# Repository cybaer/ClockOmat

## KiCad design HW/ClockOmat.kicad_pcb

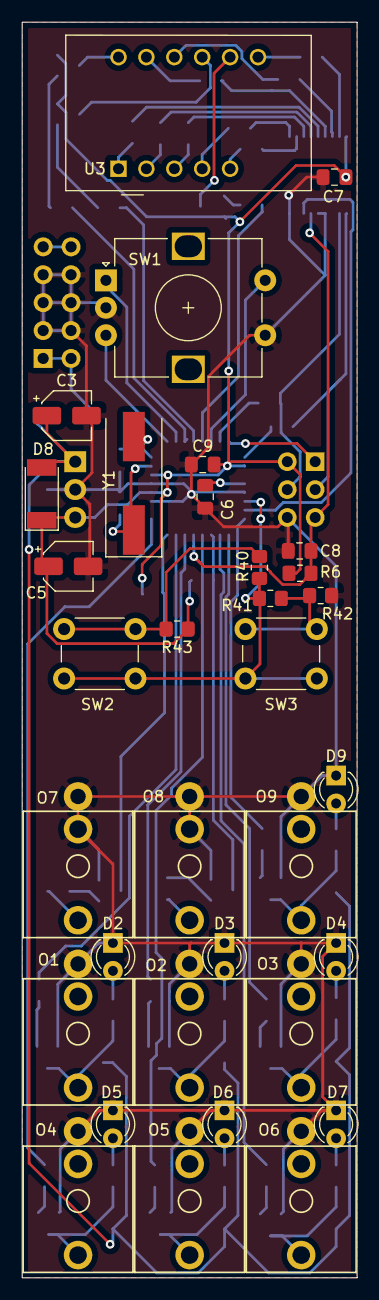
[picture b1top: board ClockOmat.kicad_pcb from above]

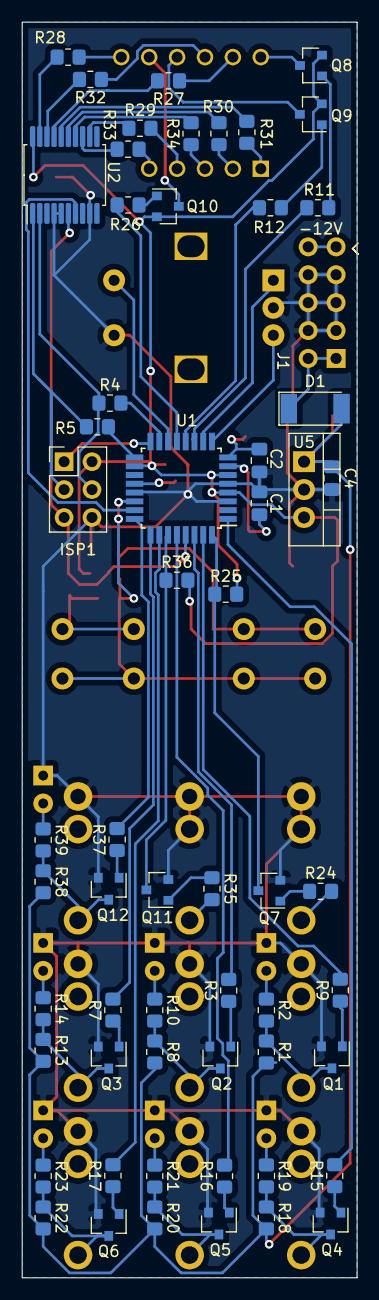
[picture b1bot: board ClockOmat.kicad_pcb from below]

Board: 2 copper layers, 30.5 x 114.3 mm, 92 parts (59 on the bottom side), 79 nets.

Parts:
C1, C2: 22p; C_0805_2012Metric_Pad1.18x1.45mm_HandSolder
C3, C5: 22µ; CP_Elec_4x5.4
C4, C6, C7, C8, C9: 100nF; C_0805_2012Metric_Pad1.18x1.45mm_HandSolder
D1, D8: DIODE; D_MELF
D2, D3, D4, D5, D6, D7, D9: LED; LED_D3.0mm
ISP1: AVR-ISP-6; PinHeader_2x03_P2.54mm_Vertical
J1: EurorackPower; EurorackPower10
O1, O2, O3, O4, O5, O6, O7, O8, O9: Thonkiconn
Q1, Q2, Q3, Q4, Q5, Q6, Q7, Q11, Q12: BC817; SOT-23
Q8, Q9, Q10: BC807; SOT-23
R1, R3, R6, R7, R8, R9, R13, R15, R16, R17, R18, R20, R22, R25, R36, R37, R38: 10K; R_0805_2012Metric_Pad1.20x1.40mm_HandSolder
R2, R10, R14, R19, R21, R23, R39: 4K7; R_0805_2012Metric_Pad1.20x1.40mm_HandSolder
R4, R5: 100; R_0805_2012Metric_Pad1.20x1.40mm_HandSolder
R11, R12, R26: 1K; R_0805_2012Metric_Pad1.20x1.40mm_HandSolder
R24, R35, R40, R41, R42: 100K; R_0805_2012Metric_Pad1.20x1.40mm_HandSolder
R27, R28, R29, R30, R31, R32, R33, R34: 330; R_0805_2012Metric_Pad1.20x1.40mm_HandSolder
R43: 47K; R_0805_2012Metric_Pad1.20x1.40mm_HandSolder
SW1: Rotary_Encoder_Switch; RotaryEncoder_Alps_EC12E-Switch_Vertical_H20mm
SW2, SW3: SW_Push; SW_PUSH_6mm_H8mm
U1: ATmega328P-AU; TQFP-32_7x7mm_P0.8mm
U2: MCP23S08-xSS-20; SSOP-20_5.3x7.2mm_P0.65mm
U3: CA56-12EWA; BA36-12LSR
U5: L7805; TO-220-3_Vertical
Y1: Crystal; Crystal_SMD_HC49-SD

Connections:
+5V: C5.1, C7.2, C9.2, D8.1, ISP1.2, Q8.2, Q9.2, Q10.2, R6.1, R25.2, R36.2, R43.1, U1.4, U1.6, U1.18, U2.20, U5.3
+12V: C3.1, C4.1, D1.2, D8.2, R1.2, R8.2, R13.2, R18.2, R20.2, R22.2, R38.2, U5.1
But: R40.2, R41.1, SW2.2, SW3.1, U1.22
CS: U1.23, U2.7
Clock: Q7.3, R25.1, U1.32
D1: Q8.3, U3.12
D2: Q9.3, U3.9
D3: Q10.3, U3.8
Dig1: R11.2, U1.11
Dig2: R12.2, U1.12
Dig3: R26.2, U1.13
ENC_A: SW1.A, U1.10
ENC_B: SW1.B, U1.9
ENC_S: SW1.S1, U1.14
GNDD: C1.1, C2.1, C3.2, C4.2, C5.2, C6.2, C7.1, C8.2, C9.1, D2.1, D3.1, D4.1, D5.1, D6.1, D7.1, D9.1, ISP1.6, J1.2, O1.3, O2.3, O3.3, O4.3, O5.3, O6.3, O7.2, O7.3, O8.2, O8.3, O9.3, Q1.2, Q2.2, Q3.2, Q4.2, Q5.2, Q6.2, Q7.2, Q11.2, Q12.2, R42.2, SW1.C, SW1.S2, U1.3, U1.5, U1.21, U2.4, U2.5, U2.9, U5.2
MISO: ISP1.1, U1.16
MOSI: ISP1.4, R4.1, U2.2
unnamed: C1.2, U1.7, Y1.1
unnamed: C2.2, U1.8, Y1.2
unnamed: C6.1, U1.20
unnamed: D1.1, J1.1
unnamed: D2.2, R2.1
unnamed: D3.2, R10.1
unnamed: D4.2, R14.1
unnamed: D5.2, R19.1
unnamed: D6.2, R21.1
unnamed: D7.2, R23.1
unnamed: D9.2, R39.1
unnamed: O1.1, Q1.3, R1.1, R2.2
unnamed: O2.1, Q2.3, R8.1, R10.2
unnamed: O3.1, Q3.3, R13.1, R14.2
unnamed: O4.1, Q4.3, R18.1, R19.2
unnamed: O5.1, Q5.3, R20.1, R21.2
unnamed: O6.1, Q6.3, R22.1, R23.2
unnamed: O7.1, R24.2
unnamed: O8.1, R35.2
unnamed: O9.1, Q12.3, R38.1, R39.2
unnamed: Q1.1, R9.1
unnamed: Q2.1, R3.1
unnamed: Q3.1, R7.1
unnamed: Q4.1, R15.1
unnamed: Q5.1, R16.1
unnamed: Q6.1, R17.1
unnamed: Q7.1, R24.1
unnamed: Q8.1, R11.1
unnamed: Q9.1, R12.1
unnamed: Q10.1, R26.1
unnamed: Q11.1, R35.1
unnamed: Q12.1, R37.1
unnamed: R4.2, U1.15
unnamed: R5.2, U1.17
unnamed: R27.1, U3.11
unnamed: R28.1, U3.7
unnamed: R29.1, U3.4
unnamed: R30.1, U3.2
unnamed: R31.1, U3.1
unnamed: R32.1, U3.10
unnamed: R33.1, U3.5
unnamed: R34.1, U3.3
unnamed: R40.1, R43.2, SW2.1
unnamed: R41.2, R42.1, SW3.2
RST: C8.1, ISP1.5, R6.2, U1.29, U2.6
Res: Q11.3, R36.1, U1.27
SCK: ISP1.3, R5.1, U2.1
a: R27.2, U2.17
b: R28.2, U2.19
c: R29.2, U2.12
d: R30.2, U2.15
e: R31.2, U2.16
f: R32.2, U2.18
g: R33.2, U2.13
out: R37.2, U1.24
out1: R9.2, U1.31
out2: R3.2, U1.30
out3: R7.2, U1.25
out4: R15.2, U1.1
out5: R16.2, U1.28
out6: R17.2, U1.26
p: R34.2, U2.14

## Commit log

2021-05-17 first release (ordered)
2021-05-18 Avrlib added
2021-05-18 lib added
2021-05-18 makefile added
2021-05-21 .gitignore added
2021-08-31 first try, display driver
2021-08-31 display._cpp removed
2021-09-17 first step: basic functionality
2021-09-17 delete
2021-09-26 quality improved
2021-09-26 decimal point added
2021-09-26 settings stored in EEPROM
2021-09-26 improved
2021-09-26 some error corrections
2021-09-26 front panel added
